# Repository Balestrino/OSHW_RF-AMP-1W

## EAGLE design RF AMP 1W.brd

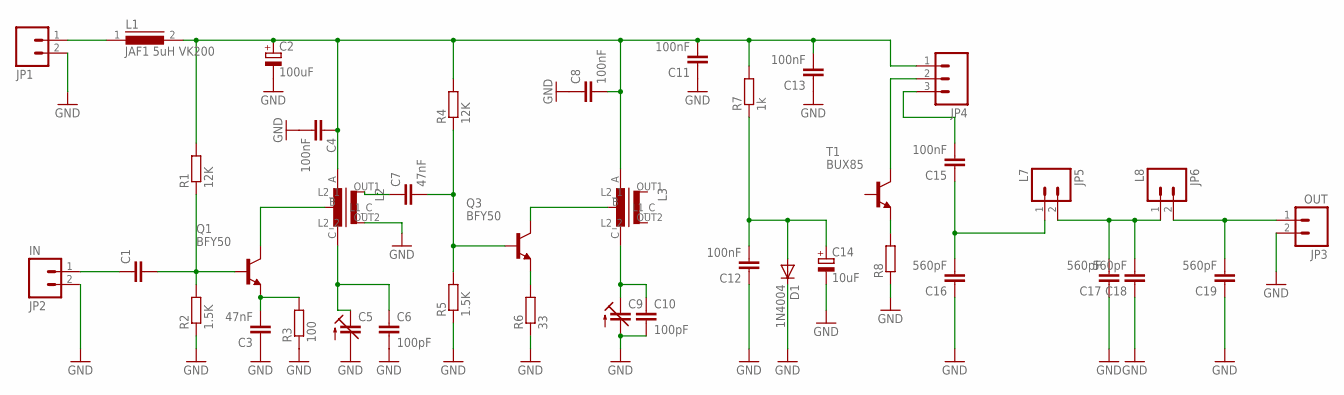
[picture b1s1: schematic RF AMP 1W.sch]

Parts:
C1: C-EU025-025X050; C025-025X050
C2: 100uF; E2-5
C3, C7: 47nF; C025-025X050
C4, C8, C11, C12, C13, C15: 100nF; C025-025X050
C5, C9: C-TRIMM808; CTRIM808-BC
C6, C10: 100pF; C025-025X050
C14: 10uF; E2-5
C16, C17, C18, C19: 560pF; C025-025X050
D1: 1N4004; DO41-10
JP1: M023.5MM; SCREWTERMINAL-3.5MM-2
JP2: IN; SCREWTERMINAL-3.5MM-2
JP3: OUT; SCREWTERMINAL-3.5MM-2
JP4: M03-SCREW-5MM; SCREWTERMINAL-5MM-3
JP5: L7; SCREWTERMINAL-5MM-2
JP6: L8; SCREWTERMINAL-5MM-2
L1: JAF1 5uH VK200; 82114A
L2, L3: ED16
Q1, Q3: BFY50; TO39
R1, R4: 12K; 0207/10
R2, R5: 1.5K; 0207/10
R3: 100; 0207/10
R6: 33; 0207/10
R7: 1k; 0207/10
R8: R-EU_0207/12; 0207/12
T1: BUX85; TO220

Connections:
GND: C2.-, C3.1, C4.2, C5.2 (A), C6.2, C8.1, C9.2 (A), C10.2, C11.1, C12.1, C13.1, C14.-, C16.1, C17.1, C18.1, C19.1, D1.C, JP1.2, JP2.2, JP3.2, L2.OUT2 (L2_2), R2.1, R3.1, R5.1, R6.1, R8.1
unnamed: JP1.1, L1.1
unnamed: C2.+, C4.1, C8.2, C11.2, C13.2, JP4.1, L1.2, L2.A (L1_1), L3.A (L1_1), R1.2, R4.2, R7.2
unnamed: C1.2, Q1.2 (B), R1.1, R2.2
unnamed: C1.1, JP2.1
unnamed: C3.2, Q1.1 (E), R3.2
unnamed: L2.B (L1_C), Q1.3 (C)
unnamed: C5.1 (E), C6.1, L2.C (L1_2)
unnamed: R8.2, T1.3 (E)
unnamed: JP4.2, T1.2 (C)
unnamed: C7.2, Q3.2 (B), R4.1, R5.2
unnamed: C15.2, JP4.3
unnamed: C15.1, C16.2, JP5.1
unnamed: Q3.1 (E), R6.2
unnamed: L3.B (L1_C), Q3.3 (C)
unnamed: C9.1 (E), C10.1, L3.C (L1_2)
unnamed: C12.2, C14.+, D1.A, R7.1
unnamed: C7.1, L2.OUT1 (L2_1)
unnamed: C17.2, C18.2, JP5.2, JP6.1
unnamed: C19.2, JP3.1, JP6.2

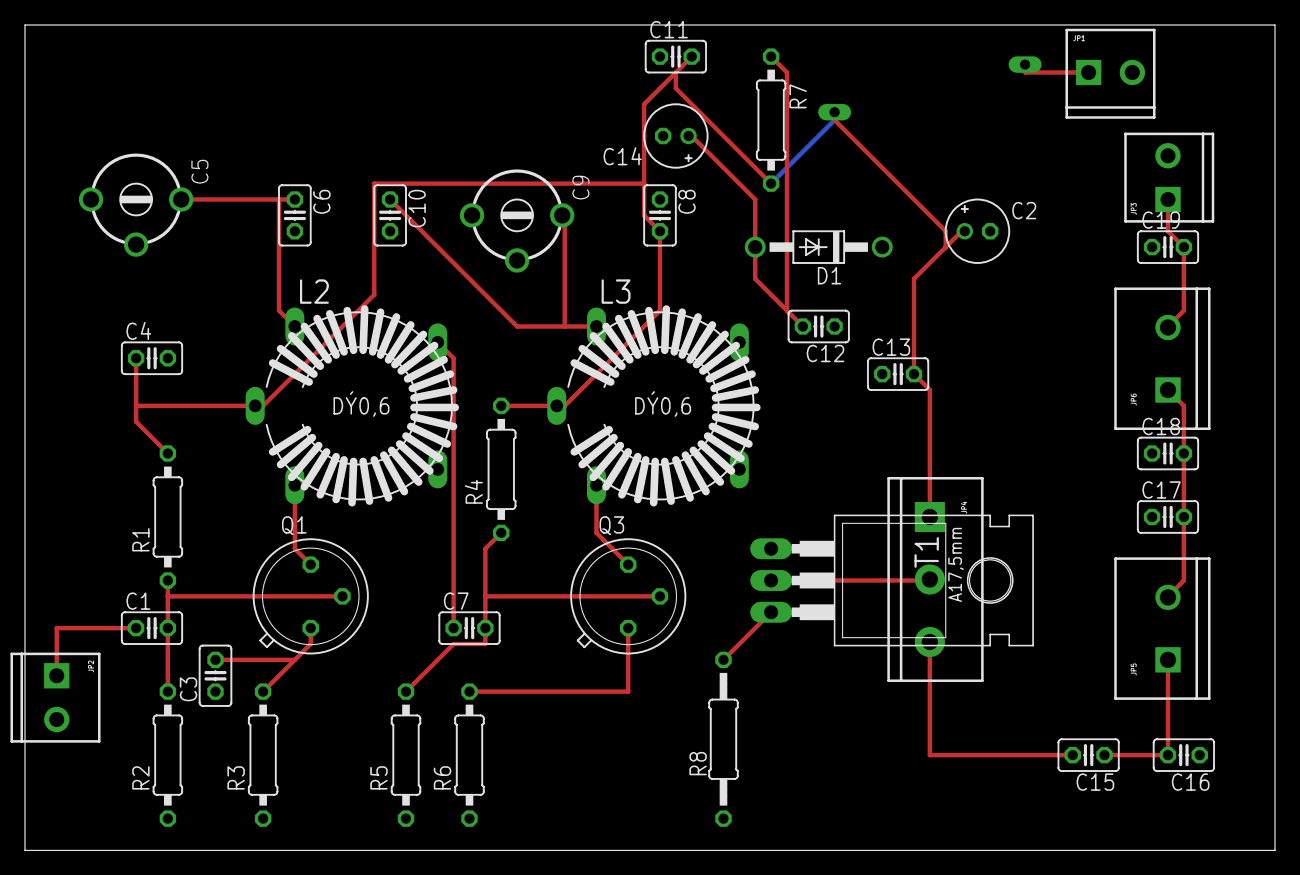
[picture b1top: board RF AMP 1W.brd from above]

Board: 2 copper layers, 100.0 x 66.0 mm, 40 parts (1 on the bottom side), 20 nets.

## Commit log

2013-06-25 Schematic
2013-06-25 PCB board file (eagle)
2013-06-25 custom inductor lib
2013-06-26 pcb layout
2013-06-28 bugfix
2013-07-08 fixed missing net, trace width 1mm

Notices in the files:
parts and their libraries:
SparkFun-Connectors: Licensing: CC v3.0 Share-Alike You are welcome to use this library for commercial purposes.
